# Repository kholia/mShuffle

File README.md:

https://rfcorner.in/posts/rethinking-tangara-music-player/

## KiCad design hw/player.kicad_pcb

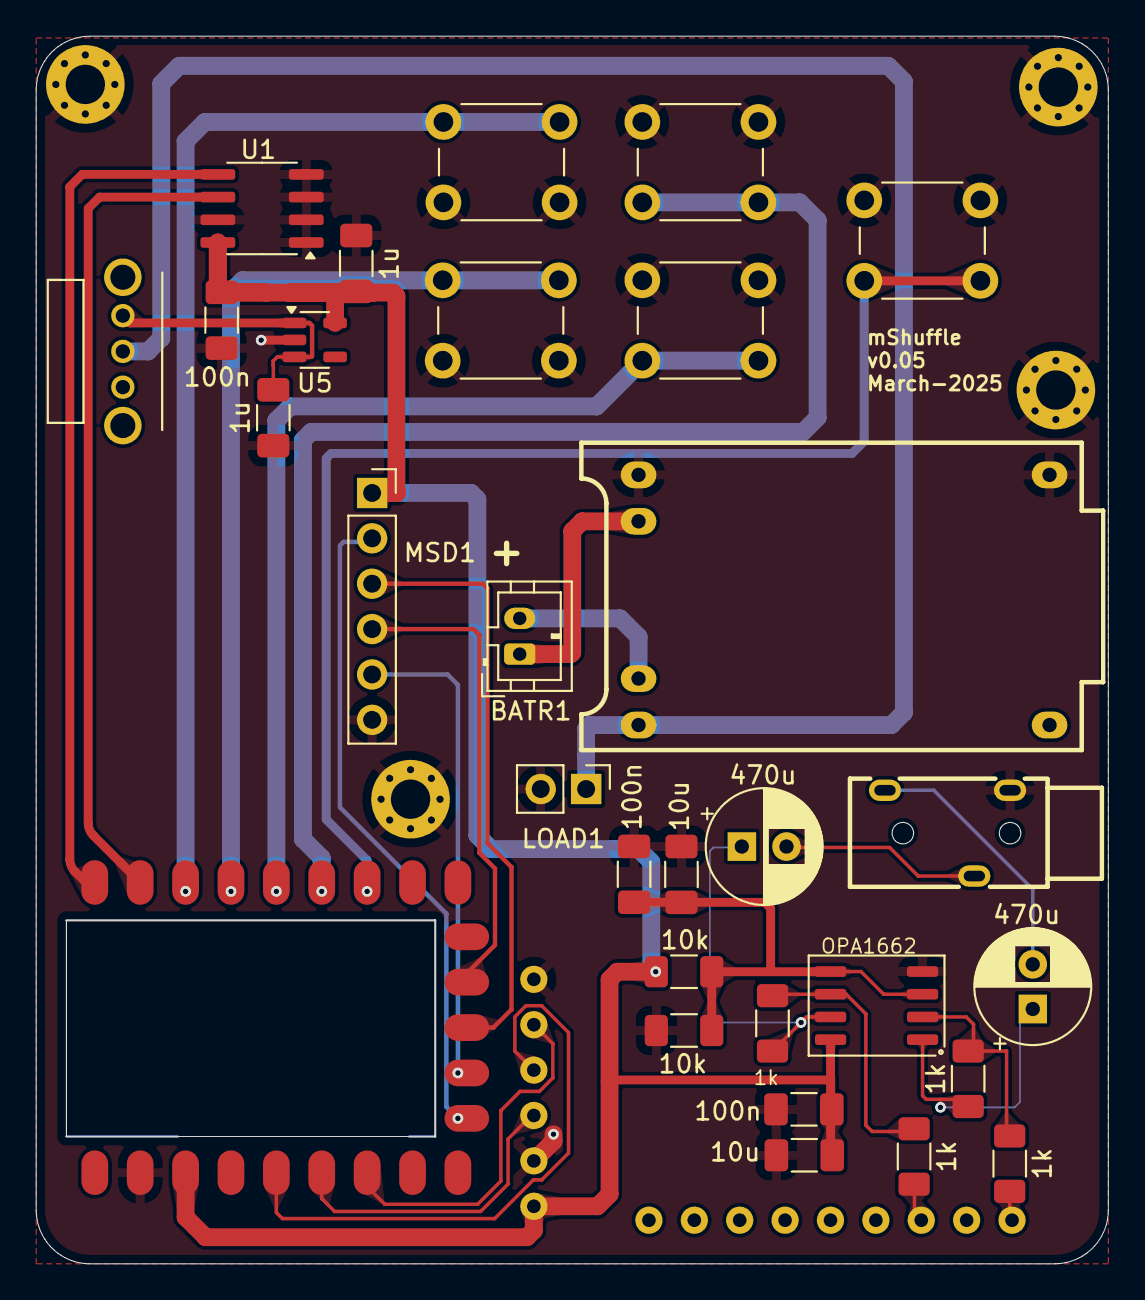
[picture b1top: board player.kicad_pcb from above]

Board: 2 copper layers, 59.9 x 68.6 mm, 35 parts (1 on the bottom side), 29 nets.

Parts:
BATR1: Conn_01x02; JST_PH_B2B-PH-K_1x02_P2.00mm_Vertical
C1, C2: 470u; CP_Radial_D6.3mm_P2.50mm
C39, C41, C45: 100n; C_1206_3216Metric_Pad1.33x1.80mm_HandSolder
C40, C42: 10u; C_1206_3216Metric_Pad1.33x1.80mm_HandSolder
C43, C44: 1u; C_1206_3216Metric_Pad1.33x1.80mm_HandSolder
CN1: PJ-3200; AUDIO-TH_PJ-3200-Fixed
H1, H2, H3, H4: MountingHole_Pad; MountingHole_2.2mm_M2_Pad_Via
LOAD1: Conn_01x02; PinHeader_1x02_P2.54mm_Vertical
MSD1: Conn_01x06_Pin; PinSocket_1x06_P2.54mm_Vertical
R1, R2, R4, R5: 1k; R_1206_3216Metric_Pad1.30x1.75mm_HandSolder
R10, R11: 10k; R_1206_3216Metric_Pad1.30x1.75mm_HandSolder
RZ1: RP2350-Zero; rp2040-zero-smd-pads-cutout-fixed
SW4, SW5, SW6, SW7, SW8: Push_Button; SW_PUSH_6mm
TP1: TP4056_USB-C_module-Fixed
U1: FM24CL64B; SOIC-8_3.9x4.9mm_P1.27mm
U2: GY-PCM5102
U3: OPA1662; SO-8_3.9x4.9mm_P1.27mm
U4: SK12D07VG4; SK12D07VG4-Fixed
U5: TLV75533PDBV; SOT-23-5

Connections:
+3.3V: C41.1, C42.1, C44.1, C45.1, MSD1.1, R10.1, RZ1.21 (3V3), U1.8 (VCC), U2.1 (Vin), U3.8 (V+), U5.5 (OUT)
GND: C39.2, C40.2, C41.2, C42.2, C43.2, C44.2, C45.2, CN1.3, H1.1, H2.1, H3.1, H4.1, LOAD1.2, MSD1.6, R11.2, RZ1.23 (GND), SW4.2, SW5.2, SW6.1, SW7.1, SW8.1, TP1.2 (-), TP1.6 (OUT-), U1.1 (A0), U1.2 (A1), U1.3 (A2), U1.4 (GND), U1.7 (WP), U2.2 (GND), U2.6 (SCK), U3.4 (V-), U5.2 (GND)
I2S_BCK: RZ1.17 (GP26), U2.5 (BCK)
I2S_DATA: RZ1.19 (GP28), U2.4 (DIN)
I2S_LCK: RZ1.18 (GP27), U2.3 (LCK)
LOAD: LOAD1.1, TP1.5 (OUT+), U4.COM
LOAD_ON: C43.1, U4.1, U5.1 (IN), U5.3 (EN)
unnamed: BATR1.1, TP1.4 (B-)
unnamed: BATR1.2, TP1.3 (B+)
unnamed: C1.1, R2.2, U3.1
unnamed: C1.2, CN1.4
unnamed: C2.1, R4.2, U3.7
unnamed: C2.2, CN1.2
unnamed: RZ1.3 (GP2), SW4.1
unnamed: RZ1.4 (GP3), SW5.1
unnamed: RZ1.5 (GP4), SW6.2
unnamed: RZ1.6 (GP5), SW7.2
unnamed: RZ1.7 (GP6), SW8.2
unnamed: R1.1, U2.15 (LOUT)
unnamed: R5.1, U2.13 (ROUT)
unnamed: R1.2, R2.1, U3.2 (-)
unnamed: R4.1, R5.2, U3.6 (-)
SCL: RZ1.2 (GP1), U1.6 (SCL)
SDA: RZ1.1 (GP0), U1.5 (SDA)
SD_CLK: MSD1.4, RZ1.11 (GP10)
SD_CS: MSD1.2, RZ1.14 (GP13)
SD_MISO: MSD1.5, RZ1.13 (GP12)
SD_MOSI: MSD1.3, RZ1.12 (GP11)
VBIAS: C39.1, C40.1, R10.2, R11.1, U3.3 (+), U3.5 (+)

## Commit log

2026-01-29 mShuffle 0.08 [WIP]
    Firmware URL:
    https://git.sr.ht/~jacqueline/tangara-fw
